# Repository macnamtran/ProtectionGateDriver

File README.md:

# 48 V Wheel Power Switch and Gate Driver

Work-in-progress KiCad design for switching the return path of a wheel module on a shared nominal 48 V bus. A 3.3 V STM32 enable signal controls an N-channel MOSFET through an Infineon 1EDN7550B gate driver powered by an assumed external regulated 12 V supply.

**Status: third PCB layout iteration (October 25, 2026). Work in progress — NOT FOR FABRICATION.**

## Latest checkpoint — third layout iteration

This checkpoint uploads the editable KiCad PCB, schematic and project settings directly from the supplied October 25 project ZIP, along with its project-local libraries and three new screenshots.

- Added C3, a 1 µF through-hole input capacitor across fused 48 V and GND.
- Added four M2 mounting holes and rounded board corners.
- Refined placement, copper zones and silkscreen.
- Proposed four-layer, 1.6 mm stackup: 2 oz outer copper and 1 oz inner copper. Actual fabrication stackup remains to be confirmed.

**Validation status:** no independent ERC/DRC, fabrication review or hardware testing was performed for this upload. Continuous-current capability is not established. The 30 A rating of the Keystone 3568 holder is a component constraint, not a verified board rating; the fuse itself and protection parts still require final selection. The native files are preserved as supplied.

## Previous checkpoint — second layout iteration

The team lead approved the schematic to proceed to layout on October 1, 2026. This update saves the second placement, routing and copper-zone iteration in `ProtectionGateDriver.kicad_pcb`, with the supplied project settings and libraries.

The scope is **one wheel per board**, with six separate one-wheel boards intended for the rover. Layout review, component-rating confirmation, current-path/thermal review and hardware validation remain outstanding. This upload is a development checkpoint, not a fabrication release. ERC/DRC were not independently rerun for this upload.

### Layout preview — iteration 2, not for fabrication

This iteration uses four copper layers (F.Cu, In1.Cu, In2.Cu and B.Cu), revised placement/routing, copper fills and ground vias. The uploaded native project files are preserved as supplied; this upload does not constitute an electrical design review.

The 3D image is a CAD preview, not a manufactured or tested board.

Previous checkpoint: [iteration 1 layout](images/layout-iteration-1.png) and [3D preview](images/layout-iteration-1-3d.png).

## Circuit overview

The description below refers to the synchronized editable KiCad files.

The intended load-current path is: J1 pin 1 (+48 V input) → fuse F1 → output_pos → J2 pin 1 → external wheel load → J2 pin 2 (output_neg) → Q1 drain → Q1 source → GND → J1 pin 2.

- Q1: MCC MCTL1D0N08Y, with custom symbol and adapted TOLL-8L footprint.
- U1: 1EDN7550B, with separate turn-on and turn-off gate resistors.
- Gate-source pulldown and Zener clamp; local driver-supply decoupling.
- J1: `48V_INPUT_XT_MALE`, with +48 V and GND input connections.
- J2: `WHEEL_OUTPUT_XT_FEMALE`, with `output_pos` and switched return `output_neg`.
- Driver supply: external regulated +12 V through J3; STM32 enable and GND through J4.
- D2 is connected between the fused positive supply and GND, after F1.
- Fuse and bus TVS are provisional and require selection against system requirements.

## Schematic preview — work in progress

Updated preview (October 9, 2026): supplied schematic showing input protection, wheel output, gate driver, test points and external supply/control connectors. Functional blocks connect through net labels. Layout refinement and hardware validation remain outstanding.

## Design calculations — preliminary

These are original working notes from the schematic, not measured results. **The corrections and limitations below take precedence over statements in the screenshots.**

### Input and gate-drive sizing

- **Arithmetic check:** `3.3² / 33,000 = 0.00033 W = 0.33 mW`, consistent with the image. The 0.10 mA figure assumes the full 3.3 V across one resistor; actual input current and resistor dissipation depend on the driver's differential input network and common-mode voltage.
- The approximately 0.85 A turn-on and 1.45 A turn-off figures are initial resistive estimates. Gate current varies during switching; `Qg / Ipeak` does not establish actual switching times. The listed 278 ns and 163 ns are rough estimates requiring waveform validation.
- `Qg / VGS` and the resulting 0.237 ms pulldown time constant are simplified approximations for a nonlinear gate. R5 discharges an undriven gate; it does not override a driver commanded high or alone guarantee safe behavior with floating control inputs.
- `236.7 nC / 0.25 V = 0.947 µF` is a first-order charge-balance estimate. Final decoupling must account for effective capacitance at 12 V, tolerance, ESR/ESL and layout; a nominal 1 µF capacitor does not guarantee that effective value.

### Gate clamp and bus protection

A nominal 15 V Zener does not by itself guarantee that gate voltage remains below 20 V. Verify its actual clamp voltage at the expected pulse current, tolerance and wiring inductance. TVS peak power (W) and pulse energy (J) must be checked separately against the transient waveform. Final fuse and TVS parts remain TBD.

## Open the project

Use KiCad 9. Open `ProtectionGateDriver.kicad_pro`, then the schematic. Keep the project files, library tables, symbol library and `ProtectionGateDriver.pretty` folder together. Both library tables use project-relative paths.

Q1 uses `ProtectionGateDriver:MCC_MCTL1D0N08Y_TOLL8L`: gate pad 1, source pads 2–8, drain pad 9. Source pads share connected copper. The footprint was adapted from KiCad's `Package_TO_SOT_SMD:Infineon_PG-HSOF-8-1`; inherited geometry and 3D model still need dimensional review. Upstream KiCad library licensing applies to derived library content; see https://www.kicad.org/libraries/license/.

## Repository baseline and completed milestones

- Received team-lead approval for the latest local schematic to proceed to PCB layout (status recorded October 1, 2026).
- Captured the low-side switching circuit and STM32 enable interface in the repository baseline.
- Synchronized the approved local schematic and project files; J1 is the 48 V input and J2 is the wheel output.
- Added a project-local MOSFET footprint with pad numbering matching the custom symbol.
- Checked edited schematic structure and connector wire paths programmatically. These checks do not replace KiCad ERC or hardware tests.

## Next steps — PCB layout and validation

- Review and refine the second PCB layout iteration; verify assigned footprints against the selected parts.
- Establish board dimensions, mounting requirements, connector positions and the intended stackup with the team.
- Place the MOSFET, gate driver, gate resistors and local decoupling to keep the gate-drive loop short; plan the load-current path and source-reference routing.
- Size copper and check clearances against confirmed electrical requirements and fabrication capabilities.

## Items to confirm and document before fabrication

Track these remaining implementation and validation items as layout proceeds.

- Confirm maximum bus voltage, wheel continuous/stall current, and whether the switched load is a motor or a motor controller.
- Select fuse and TVS ratings; assess the turn-off transient path and MOSFET voltage margin.
- Resolve the lead's AGND/DGND guidance and the system ground connection. The current schematic connects R2 to GND and J4 provides STM32 enable and GND; verify compatibility with the system grounding architecture.
- Verify MOSFET footprint dimensions against the manufacturer drawing.
- Complete remaining footprint assignments, KiCad ERC, PCB layout, thermal/current-path review and DRC.
- Define and carry out bench validation before claiming measured performance.

An RC snubber is not present in this revision. No simulation or measured performance is claimed.

## References

- [MCC MCTL1D0N08Y datasheet](https://www.mccsemi.com/pdf/Products/MCTL1D0N08Y(TOLL-8L).pdf)
- [Infineon 1EDN7550B datasheet](https://www.infineon.com/dgdl/Infineon-1EDN7550B-DS-v02_00-EN.pdf?fileId=5546d46262b31d2e01635d9799ef264f)

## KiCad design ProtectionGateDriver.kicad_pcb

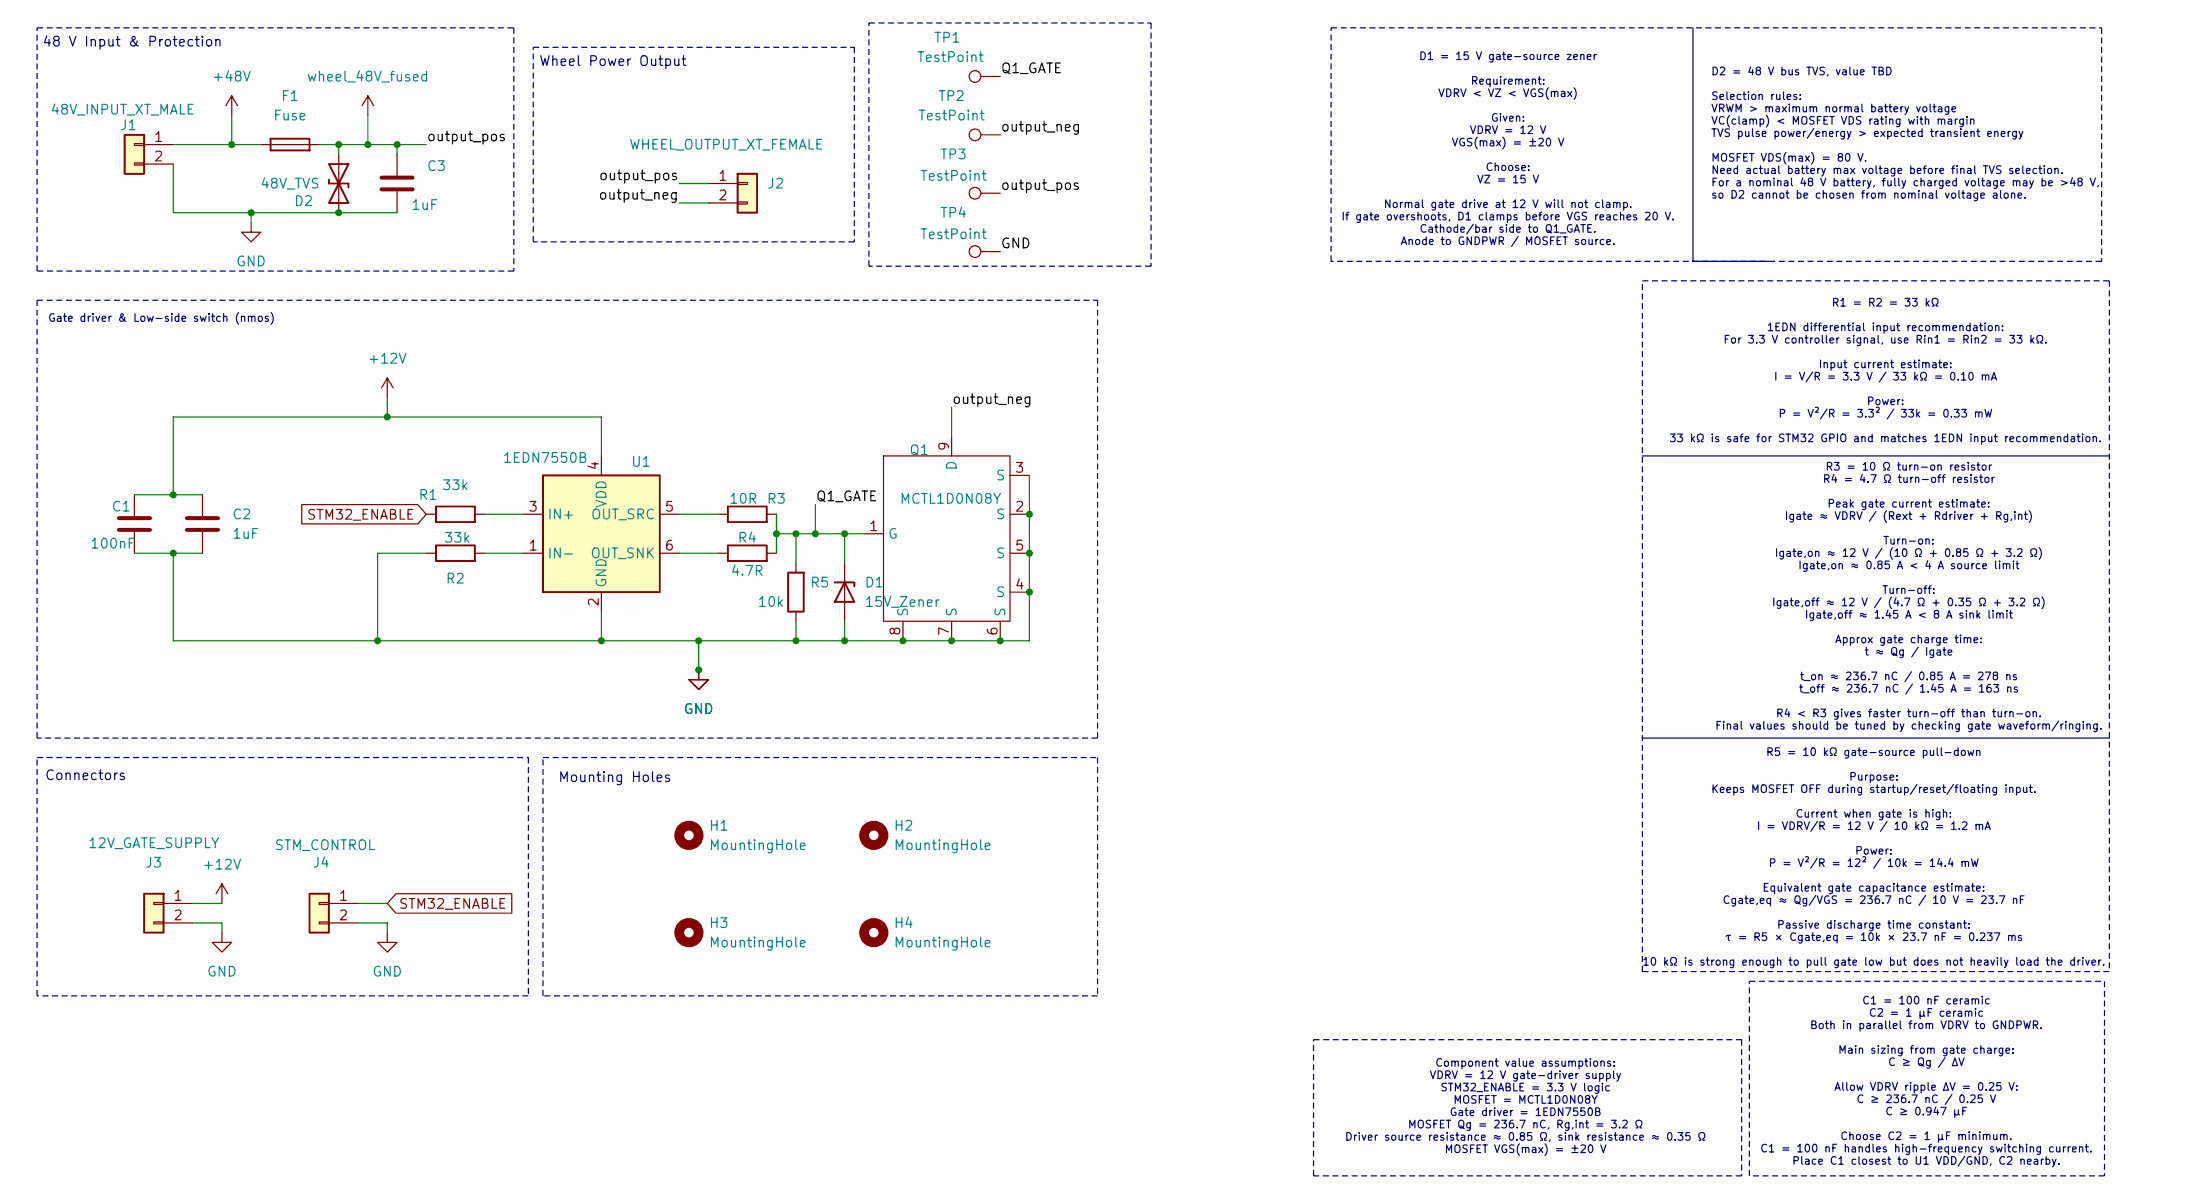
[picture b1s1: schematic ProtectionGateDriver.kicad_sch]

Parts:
C1: 100nF; C_0805_2012Metric
C2: 1uF; C_0805_2012Metric
C3: 1uF; C_Rect_L13.0mm_W8.0mm_P10.00mm_FKS3_FKP3_MKS4; MPN ECQ-E1105KF
D1: 15V_Zener; D_SOD-123
D2: 48V_TVS; D_SMB
F1: Fuse; Fuseholder_Blade_Mini_Keystone_3568
H1, H2, H3, H4: MountingHole; MountingHole_2.2mm_M2
J1: 48V_INPUT_XT_MALE; AMASS_XT60-M_1x02_P7.20mm_Vertical
J2: WHEEL_OUTPUT_XT_FEMALE; AMASS_XT60-F_1x02_P7.20mm_Vertical
J3: 12V_GATE_SUPPLY; JST_XH_B2B-XH-A_1x02_P2.50mm_Vertical
J4: STM_CONTROL; PinHeader_1x02_P2.54mm_Vertical
Q1: MCTL1D0N08Y; MCC_MCTL1D0N08Y_TOLL8L
R1, R2: 33k; R_0805_2012Metric
R3: 10R; R_0805_2012Metric
R4: 4.7R; R_0805_2012Metric
R5: 10k; R_0805_2012Metric
TP1, TP2, TP3, TP4: TestPoint; TestPoint_Pad_D1.0mm
U1: 1EDN7550B; SOT-23-6

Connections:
+12V: C1.1, C2.1, J3.1, U1.4 (VDD)
+48V: F1.1, J1.1
/Q1_GATE: D1.1 (K), Q1.1 (G), R3.2, R4.2, R5.2, TP1.1 (1_1)
/output_neg: J2.2, Q1.9 (D), TP2.1 (1_1)
GND: C1.2, C2.2, C3.2, D1.2 (A), D2.2 (A2), J1.2, J3.2, J4.2, Q1.2 (S), Q1.3 (S), Q1.4 (S), Q1.5 (S), Q1.6 (S), Q1.7 (S), Q1.8 (S), R2.1, R5.1, TP4.1 (1_1), U1.2 (GND)
unnamed: R1.2, U1.3 (IN+)
unnamed: R2.2, U1.1 (IN-)
unnamed: R4.1, U1.6 (OUT_SNK)
unnamed: R3.1, U1.5 (OUT_SRC)
STM32_ENABLE: J4.1, R1.1
wheel_48V_fused: C3.1, D2.1 (A1), F1.2, J2.1, TP3.1 (1_1)

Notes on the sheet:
R5 = 10 kΩ gate-source pull-down Purpose: Keeps MOSFET OFF during startup/reset/floating input. Current when gate is high: I = VDRV/R = 12 V / 10 kΩ = 1.2 mA Power: P = V²/R = 12² / 10k = 14.4 mW Equivalent gate capacitance estimate: Cgate,eq ≈ Qg/VGS = 236.7 nC / 10 V = 23.7 nF Passive discharge t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
D1 = 15 V gate-source zener Requirement: VDRV < VZ < VGS(max) Given: VDRV = 12 V VGS(max) = ±20 V Choose: VZ = 15 V Normal gate drive at 12 V will not clamp. If gate overshoots, D1 clamps before VGS reaches 20 V. Cathode/bar side to Q1_GATE. Anode to GNDPWR / MOSFET source.
48 V Input & Protection
Wheel Power Output
C1 = 100 nF ceramic C2 = 1 µF ceramic Both in parallel from VDRV to GNDPWR. Main sizing from gate charge: C ≥ Qg / ΔV Allow VDRV ripple ΔV = 0.25 V: C ≥ 236.7 nC / 0.25 V C ≥ 0.947 µF Choose C2 = 1 µF minimum. C1 = 100 nF handles high-frequency switching current. Place C1 closest to U1 VDD/GND, C2 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
D2 = 48 V bus TVS, value TBD Selection rules: VRWM > maximum normal battery voltage VC(clamp) < MOSFET VDS rating with margin TVS pulse power/energy > expected transient energy MOSFET VDS(max) = 80 V. Need actual battery max voltage before final TVS selection. For a nominal 48 V battery, fully char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
Connectors
R3 = 10 Ω turn-on resistor R4 = 4.7 Ω turn-off resistor Peak gate current estimate: Igate ≈ VDRV / (Rext + Rdriver + Rg,int) Turn-on: Igate,on ≈ 12 V / (10 Ω + 0.85 Ω + 3.2 Ω) Igate,on ≈ 0.85 A < 4 A source limit Turn-off: Igate,off ≈ 12 V / (4.7 Ω + 0.35 Ω + 3.2 Ω) Igate,off ≈ 1.45 A < 8 A sink li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
Gate driver & Low-side switch (nmos)
R1 = R2 = 33 kΩ 1EDN differential input recommendation: For 3.3 V controller signal, use Rin1 = Rin2 = 33 kΩ. Input current estimate: I = V/R = 3.3 V / 33 kΩ = 0.10 mA Power: P = V²/R = 3.3² / 33k = 0.33 mW 33 kΩ is safe for STM32 GPIO and matches 1EDN input recommendation.
Mounting Holes
Component value assumptions: VDRV = 12 V gate-driver supply STM32_ENABLE = 3.3 V logic MOSFET = MCTL1D0N08Y Gate driver = 1EDN7550B MOSFET Qg = 236.7 nC, Rg,int = 3.2 Ω Driver source resistance ≈ 0.85 Ω, sink resistance ≈ 0.35 Ω MOSFET VGS(max) = ±20 V

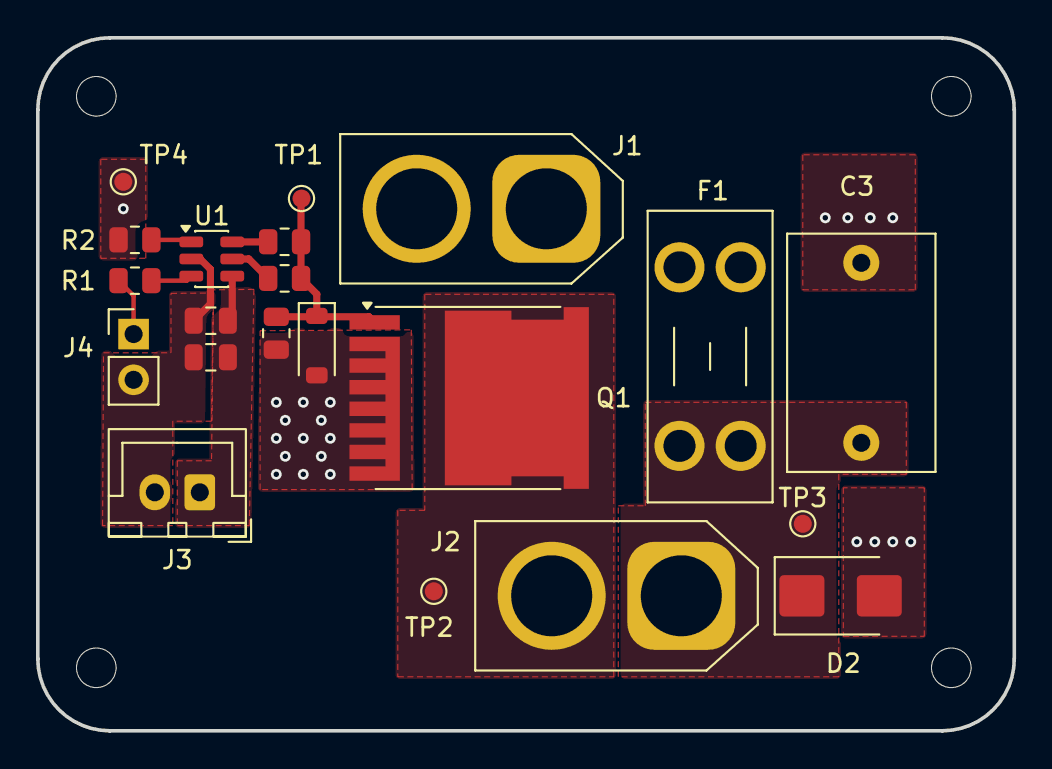
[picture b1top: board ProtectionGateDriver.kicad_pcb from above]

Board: 4 copper layers, 54.2 x 38.5 mm, 25 parts (0 on the bottom side), 11 nets.
